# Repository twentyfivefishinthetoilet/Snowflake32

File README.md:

# Snowflake32
an ESP32-S3 devboard created for Hack Club's [Holiday Hardware Swap](https://swap.hackclub.com/). program it with the .ino file in /firmware and watch snowflakes fall on your board!

## features
- MICRO SD/TF CARD slot (spi)
- BATTERY CHARGING MODULE + IMPLEMENTATION
- EXTRA POWER PINS
- 3 CONTROLLED LEDS
- ESP32-S3-WROOM-1-N16R8 STUFF (wifi, BLE, 16mb flash and 8mb psram, etc.)

## schematic preview

*close up on the male header pinout*

*please note that the actual headers look something like this:*
```
| 1 | 2 |
| 3 | 4 |
...
```

## pcb layout preview

*find the actual files in /pcb*

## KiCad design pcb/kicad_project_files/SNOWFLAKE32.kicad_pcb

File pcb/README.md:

all of the kicad files will be here (libraries, sch and pcb files, etc.)

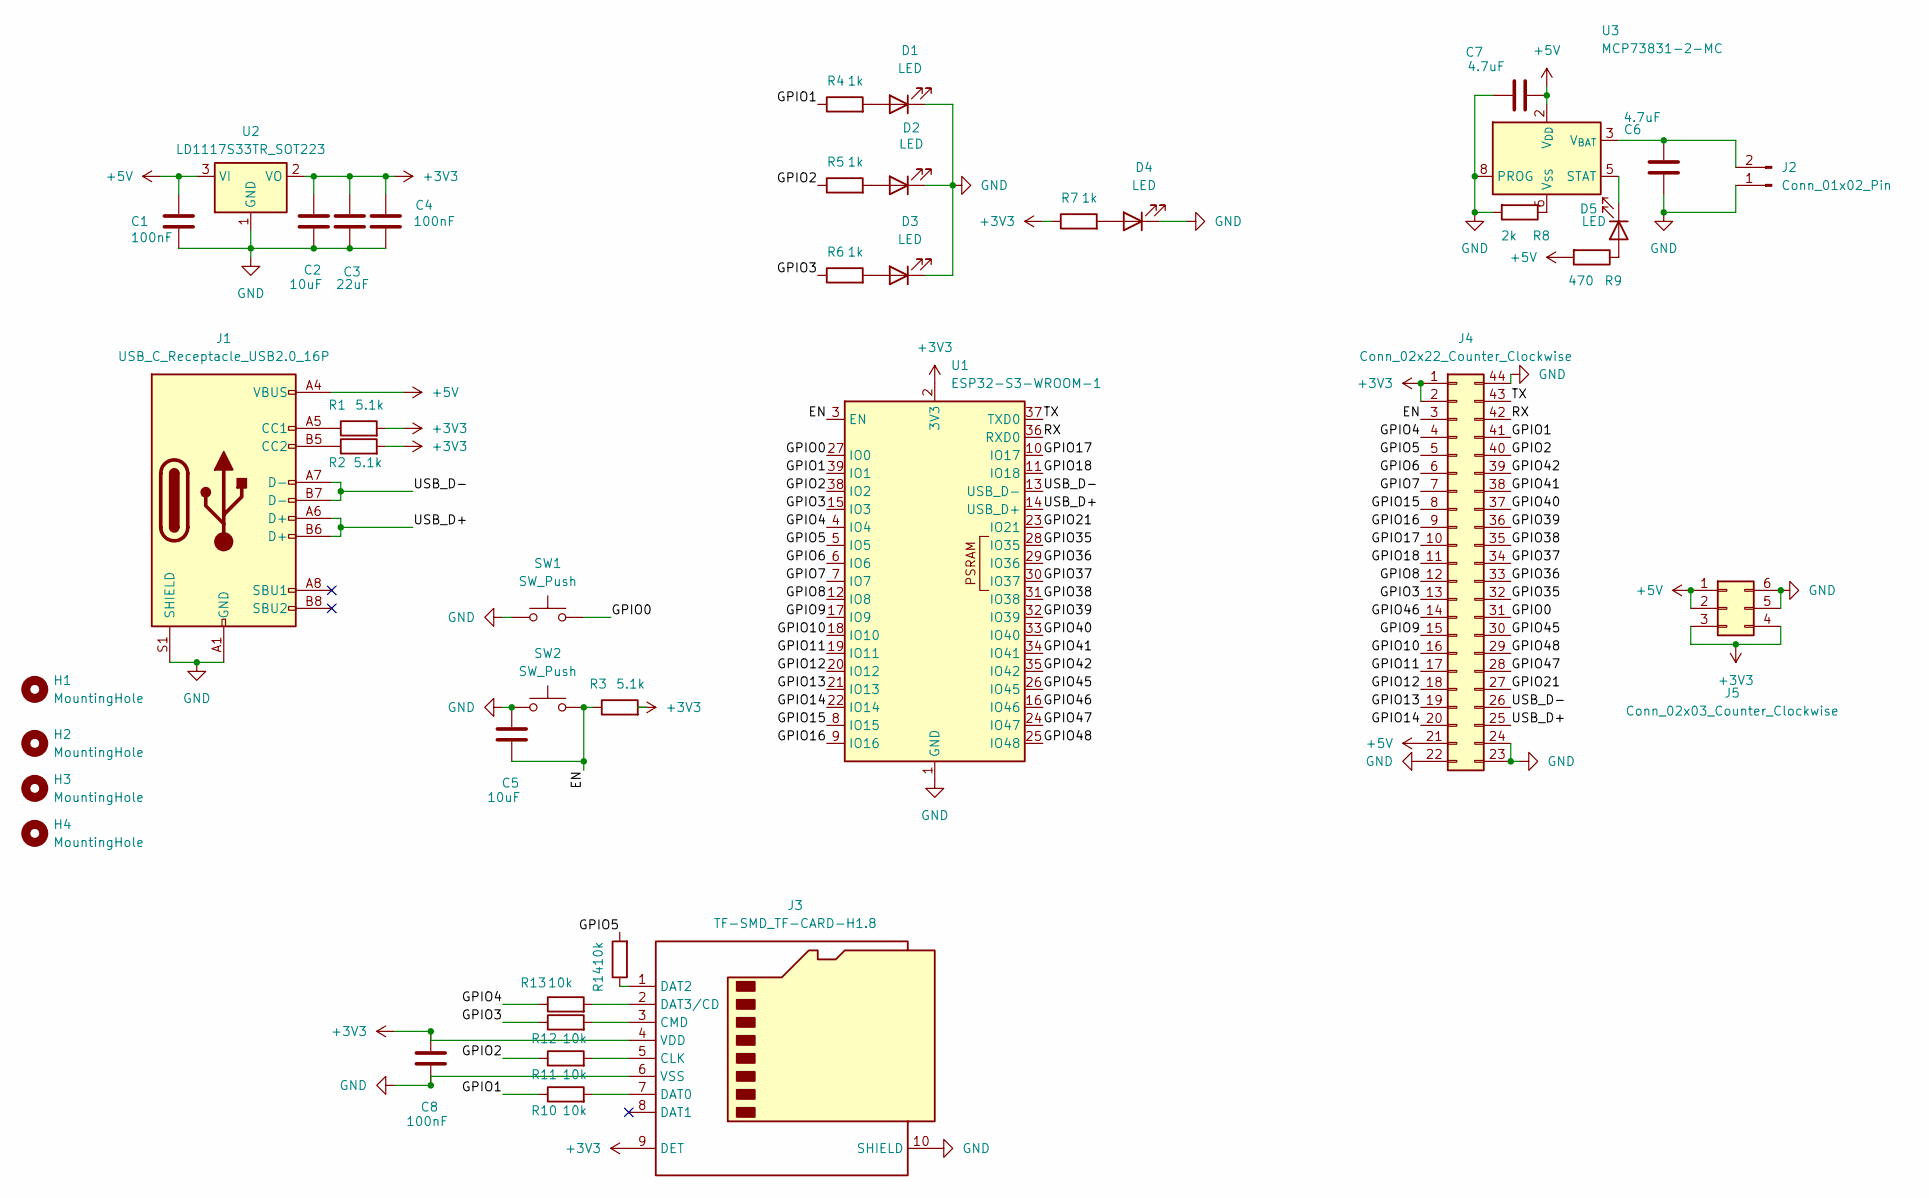
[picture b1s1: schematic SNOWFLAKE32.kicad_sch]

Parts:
C1, C4, C8: 100nF; C_0603_1608Metric; LCSC C14663
C2, C5: 10uF; C_0603_1608Metric; LCSC C109457
C3: 22uF; C_0603_1608Metric; LCSC C109448
C6, C7: 4.7uF; C_0603_1608Metric; LCSC C109457
D1, D2, D3, D4, D5: LED; LED_0603_1608Metric; LCSC C2290
H1, H2, H3, H4: MountingHole; MountingHole_2.5mm
J1: USB_C_Receptacle_USB2.0_16P; USB_C_Receptacle_HCTL_HC-TYPE-C-16P-01A; LCSC C165948
J2: Conn_01x02_Pin; CONN-TH_2P-P2.50_HX-2.54MM-2P-ZZ-MS; LCSC C7543455
J3: TF-SMD_TF-CARD-H1.8; LCSC C7529389
J4: Conn_02x22_Counter_Clockwise; PinHeader_2x22_P2.54mm_Vertical; LCSC C19630950
J5: Conn_02x03_Counter_Clockwise; PinHeader_2x03_P2.54mm_Vertical; LCSC C5116479
R1, R2, R3: 5.1k; R_0603_1608Metric; LCSC C105580
R4, R5, R6, R7: 1k; R_0603_1608Metric; LCSC C22548
R8: 2k; R_0603_1608Metric; LCSC C105580
R9: 470; R_0603_1608Metric; LCSC C105580
R10, R11, R12, R13, R14: 10k; R_0603_1608Metric; LCSC C105580
SW1, SW2: SW_Push; SW-SMD_HX-3X6X2.5-X; LCSC C49234125
U1: ESP32-S3-WROOM-1; LCSC C2913202
U2: LD1117S33TR_SOT223; SOT-223-3_TabPin2; LCSC C86781
U3: MCP73831-2-MC; DFN-8-1EP_3x2mm_P0.5mm_EP1.7x1.4mm; LCSC C150772

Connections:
+3V3: C2.1, C3.1, C4.1, C8.1, J3.4 (VDD), J3.9 (DET), J4.1, J4.2, J5.3, J5.4, R1.2, R2.2, R3.2, R7.1, U1.2 (3V3), U2.2 (VO)
+5V: C1.1, C7.2, J1.A4 (VBUS), J1.A9 (VBUS), J1.B4 (VBUS), J1.B9 (VBUS), J4.21, J5.1, J5.2, R9.2, U2.3 (VI), U3.1 (V_{DD}), U3.2 (V_{DD})
/EN: C5.2, J4.3, R3.1, SW2.2, U1.3 (EN)
/GPIO0: J4.31, SW1.2, U1.27 (IO0)
/GPIO1: J4.41, R4.1, R10.1, U1.39 (IO1)
/GPIO2: J4.40, R5.1, R11.1, U1.38 (IO2)
/GPIO3: J4.13, R6.1, R12.1, U1.15 (IO3)
/GPIO4: J4.4, R13.1, U1.4 (IO4)
/GPIO5: J4.5, R14.2, U1.5 (IO5)
/GPIO6: J4.6, U1.6 (IO6)
/GPIO7: J4.7, U1.7 (IO7)
/GPIO8: J4.12, U1.12 (IO8)
/GPIO9: J4.15, U1.17 (IO9)
/GPIO10: J4.16, U1.18 (IO10)
/GPIO11: J4.17, U1.19 (IO11)
/GPIO12: J4.18, U1.20 (IO12)
/GPIO13: J4.19, U1.21 (IO13)
/GPIO14: J4.20, U1.22 (IO14)
/GPIO15: J4.8, U1.8 (IO15)
/GPIO16: J4.9, U1.9 (IO16)
/GPIO17: J4.10, U1.10 (IO17)
/GPIO18: J4.11, U1.11 (IO18)
/GPIO21: J4.27, U1.23 (IO21)
/GPIO35: J4.32, U1.28 (IO35)
/GPIO36: J4.33, U1.29 (IO36)
/GPIO37: J4.34, U1.30 (IO37)
/GPIO38: J4.35, U1.31 (IO38)
/GPIO39: J4.36, U1.32 (IO39)
/GPIO40: J4.37, U1.33 (IO40)
/GPIO41: J4.38, U1.34 (IO41)
/GPIO42: J4.39, U1.35 (IO42)
/GPIO45: J4.30, U1.26 (IO45)
/GPIO46: J4.14, U1.16 (IO46)
/GPIO47: J4.28, U1.24 (IO47)
/GPIO48: J4.29, U1.25 (IO48)
/RX: J4.42, U1.36 (RXD0)
/TX: J4.43, U1.37 (TXD0)
/USB_D+: J1.A6 (D+), J1.B6 (D+), J4.25, U1.14 (USB_D+)
/USB_D-: J1.A7 (D-), J1.B7 (D-), J4.26, U1.13 (USB_D-)
GND: C1.2, C2.2, C3.2, C4.2, C5.1, C6.1, C7.1, C8.2, D1.1 (K), D2.1 (K), D3.1 (K), D4.1 (K), J1.A1 (GND), J1.A12 (GND), J1.B1 (GND), J1.B12 (GND), J1.S1 (SHIELD), J2.1, J3.6 (VSS), J3.10 (SHIELD), J3.11, J3.12, J3.13, J4.22, J4.23, J4.24, J4.44, J5.5, J5.6, R8.2, SW1.1, SW2.1, U1.1 (GND), U1.40 (GND), U1.41 (GND), U2.1 (GND), U3.8 (PROG)
unnamed: D1.2 (A), R4.2
unnamed: D2.2 (A), R5.2
unnamed: D3.2 (A), R6.2
unnamed: D4.2 (A), R7.2
unnamed: D5.2 (A), R9.1
unnamed: D5.1 (K), U3.5 (STAT)
unnamed: J1.A5 (CC1), R1.1
unnamed: J1.B5 (CC2), R2.1
unnamed: C6.2, J2.2, U3.3 (V_{BAT}), U3.4 (V_{BAT})
unnamed: J3.5 (CLK), R11.2
unnamed: J3.3 (CMD), R12.2
unnamed: J3.7 (DAT0), R10.2
unnamed: J3.1 (DAT2), R14.1
unnamed: J3.2 (DAT3/CD), R13.2
unnamed: R8.1, U3.6 (V_{SS})

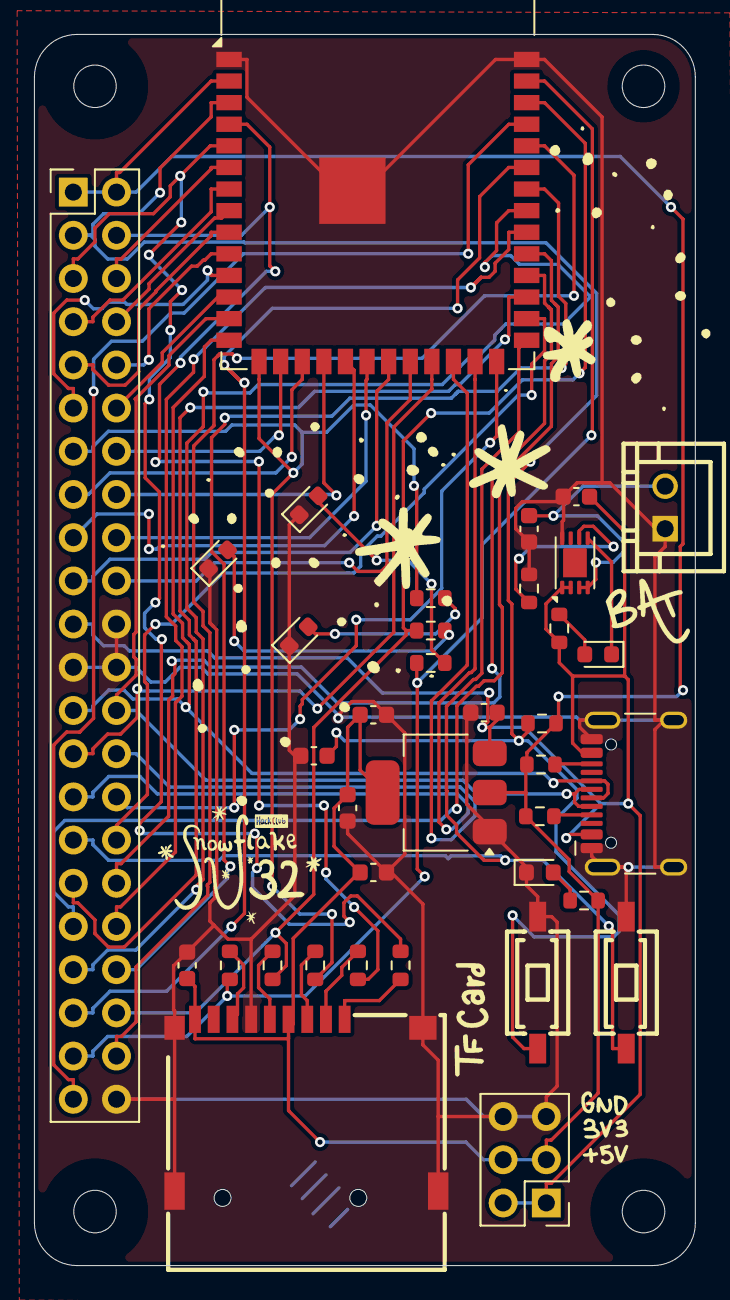
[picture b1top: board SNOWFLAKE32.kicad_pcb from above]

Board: 2 copper layers, 38.9 x 72.4 mm, 41 parts (0 on the bottom side), 55 nets.

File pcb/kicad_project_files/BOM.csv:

Comment,Designator,Footprint,LCSC,Quantity
100nF,"C1,C4",C_0603_1608Metric,C14663,2
100nF,C8,C_0603_1608Metric,C1590,1
10k,"R10,R11,R12,R13,R14",R_0603_1608Metric,C15401,5
10uF,C5,C_0603_1608Metric,C109457,1
10uF,C2,C_0603_1608Metric,C19702,1
1k,"R4,R5,R6,R7",R_0603_1608Metric,C22548,4
22uF,C3,C_0603_1608Metric,C59461,1
2k,R8,R_0603_1608Metric,C22975,1
4.7uF,"C6,C7",C_0603_1608Metric,C1705,2
470,R9,R_0603_1608Metric,C23179,1
5.1k,"R1,R2,R3",R_0603_1608Metric,C105580,3
Conn_01x02_Pin,J2,CONN-TH_2P-P2.50_HX-2.54MM-2P-ZZ-MS,C7543455,1
Conn_02x03_Counter_Clockwise,J5,PinHeader_2x03_P2.54mm_Vertical,C5116479,1
Conn_02x22_Counter_Clockwise,J4,PinHeader_2x22_P2.54mm_Vertical,C7430418,1
ESP32-S3-WROOM-1,U1,ESP32-S3-WROOM-1,C2913202,1
LD1117S33TR_SOT223,U2,SOT-223-3_TabPin2,C86781,1
LED,"D1,D2,D3,D4,D5",LED_0603_1608Metric,C2290,5
MCP73831-2-MC,U3,DFN-8-1EP_3x2mm_P0.5mm_EP1.7x1.4mm,C150772,1
SW_Push,"SW1,SW2",SW-SMD_HX-3X6X2.5-X,C49234125,2
TF-SMD_TF-CARD-H1.8,J3,TF-SMD_TF-CARD-H1.8,C7529389,1
USB_C_Receptacle_USB2.0_16P,J1,USB_C_Receptacle_HCTL_HC-TYPE-C-16P-01A,C165948,1
